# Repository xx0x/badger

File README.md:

# The Badger

The Badger is an open-source synth that packs 18 presets – synths, drums, and drones – into a small, pocketable device. Use the knobs to steer its internal generative sequencer and tweak the melodies yourself, or hit the randomizer to discover new patterns and textures at the press of a button. It also comes with MIDI (both TRS and USB), CV, and clock connections for patching into a bigger setup – or chaining multiple Badgers together. The audio is not particularly hi-fi, but that's exactly where the fun lives. Take it with a grain of salt, but: “the cheapest, *fully featured* synth ever.”

See [badger-quick-guide-en.pdf](./manuals/badger-quick-guide-en.pdf) for the quick guide.

See [badger-full-manual-en.md](./manuals/badger-full-manual-en.md) or [badger-full-manual-en.pdf](./manuals/badger-full-manual-en.pdf) for the full user manual (controls, presets, MIDI...).

## Technical Specs

- PY32F071C1BU6TR ARM Cortex M0+
- 48 MHz clock speed
- 16 kB RAM, 128 kB FLASH
- 256 B EEPROM to store settings
- MIDI in, MIDI out (TRS Jack, Type A)
- USB MIDI
- Stereo audio out using a 12-bit DAC
- Headphone amplifier with 200mW per channel at 32Ω load
- Patch points for analog clock in and out
- Banana-style holes for CV IN (0.25V to 5V), ground, True (5V ref), False (0V ref)

## Schematic

## Firmware update

Download the UF2 firmware from the *Releases*. Connect The Badger to your computer, hold *PREV* and turn the device on. The *PREV* LED should light red. Then just drag the UF2 file onto the *BADGERBOOT* drive. This applies to already built Badgers. When you build your own Badger from scratch, you need to flash the bootloader first. See [HOW_TO_DEVELOP.md](./HOW_TO_DEVELOP.md).

## Where to get it?

The Badger DIY kit is not available for purchase yet, so follow for updates.

But you can already make your own by downloading the manufacturing files from the `pcb` directory and have the PCB manufactured yourself.

## AI usage and transparency

All creative decisions – sound design, controls and layouts – were made by the author. AI tools (specifically Claude Opus 5 and 5.5) were used to help write parts of the code, fix bugs, validate the electronics design and write documentation. All AI-assisted work was reviewed and tested by the author.

## License

| What                                   | Where                                                         | License                                                   |
| -------------------------------------- | ------------------------------------------------------------- | --------------------------------------------------------- |
| Code                                   | `code/`, `utils/`                                             | MIT, see [LICENSE](./LICENSE)                             |
| Hardware design                        | `pcb/`                                                        | CERN-OHL-P-2.0, see [LICENSE-CERN-OHL-P-2.0](./LICENSE-CERN-OHL-P-2.0) |
| Documentation, manuals, images, 3D files | `manuals/`, `images/`, `3d_models/`, `*.md`                 | CC BY 4.0, see [LICENSE-CC-BY-4.0](./LICENSE-CC-BY-4.0)   |

Third-party components listed below keep their own licenses.

## Third-party components

| Component                                                                   | Where                                                                         | License                                                             |
| --------------------------------------------------------------------------- | ----------------------------------------------------------------------------- | ------------------------------------------------------------------- |
| CMSIS (Arm)                                                                 | `code/lib/CMSIS` (except `Device`)                                            | Apache-2.0                                                          |
| PY32F071 HAL driver, CMSIS device files, linker script (Puya Semiconductor) | `code/lib/PY32F071_HAL_Driver`, `code/lib/CMSIS/Device`, `code/lib/LDScripts` | BSD-3-Clause, see [LICENSE](./code/lib/PY32F071_HAL_Driver/LICENSE) |
| PY32 J-Link device support files (Puya Semiconductor)                       | `code/misc/JLinkDevices`                                                      | © Puya Semiconductor                                                |
| TinyUSB                                                                     | `code/lib/tinyusb` (submodule)                                                | MIT                                                                 |
| UF2 (Microsoft)                                                             | `code/lib/uf2` (submodule)                                                    | MIT                                                                 |
| TinyUF2 bootloader (Badger port)                                            | `code/bootloader` (prebuilt)                                                  | MIT                                                                 |
| Dosis font                                                                  | `utils/fonts/Dosis`                                                           | SIL OFL 1.1, see [OFL.txt](./utils/fonts/Dosis/OFL.txt)             |
| UnifrakturCook font (j. 'mach' wust, Peter Wiegel)                          | `utils/fonts/UnifrakturCook`                                                  | SIL OFL 1.1, see [OFL.txt](./utils/fonts/UnifrakturCook/OFL.txt)    |
| Component 3D models (from their manufacturers)                              | `pcb/badger_v2/3d_models`                                                     | Their respective owners                                             |

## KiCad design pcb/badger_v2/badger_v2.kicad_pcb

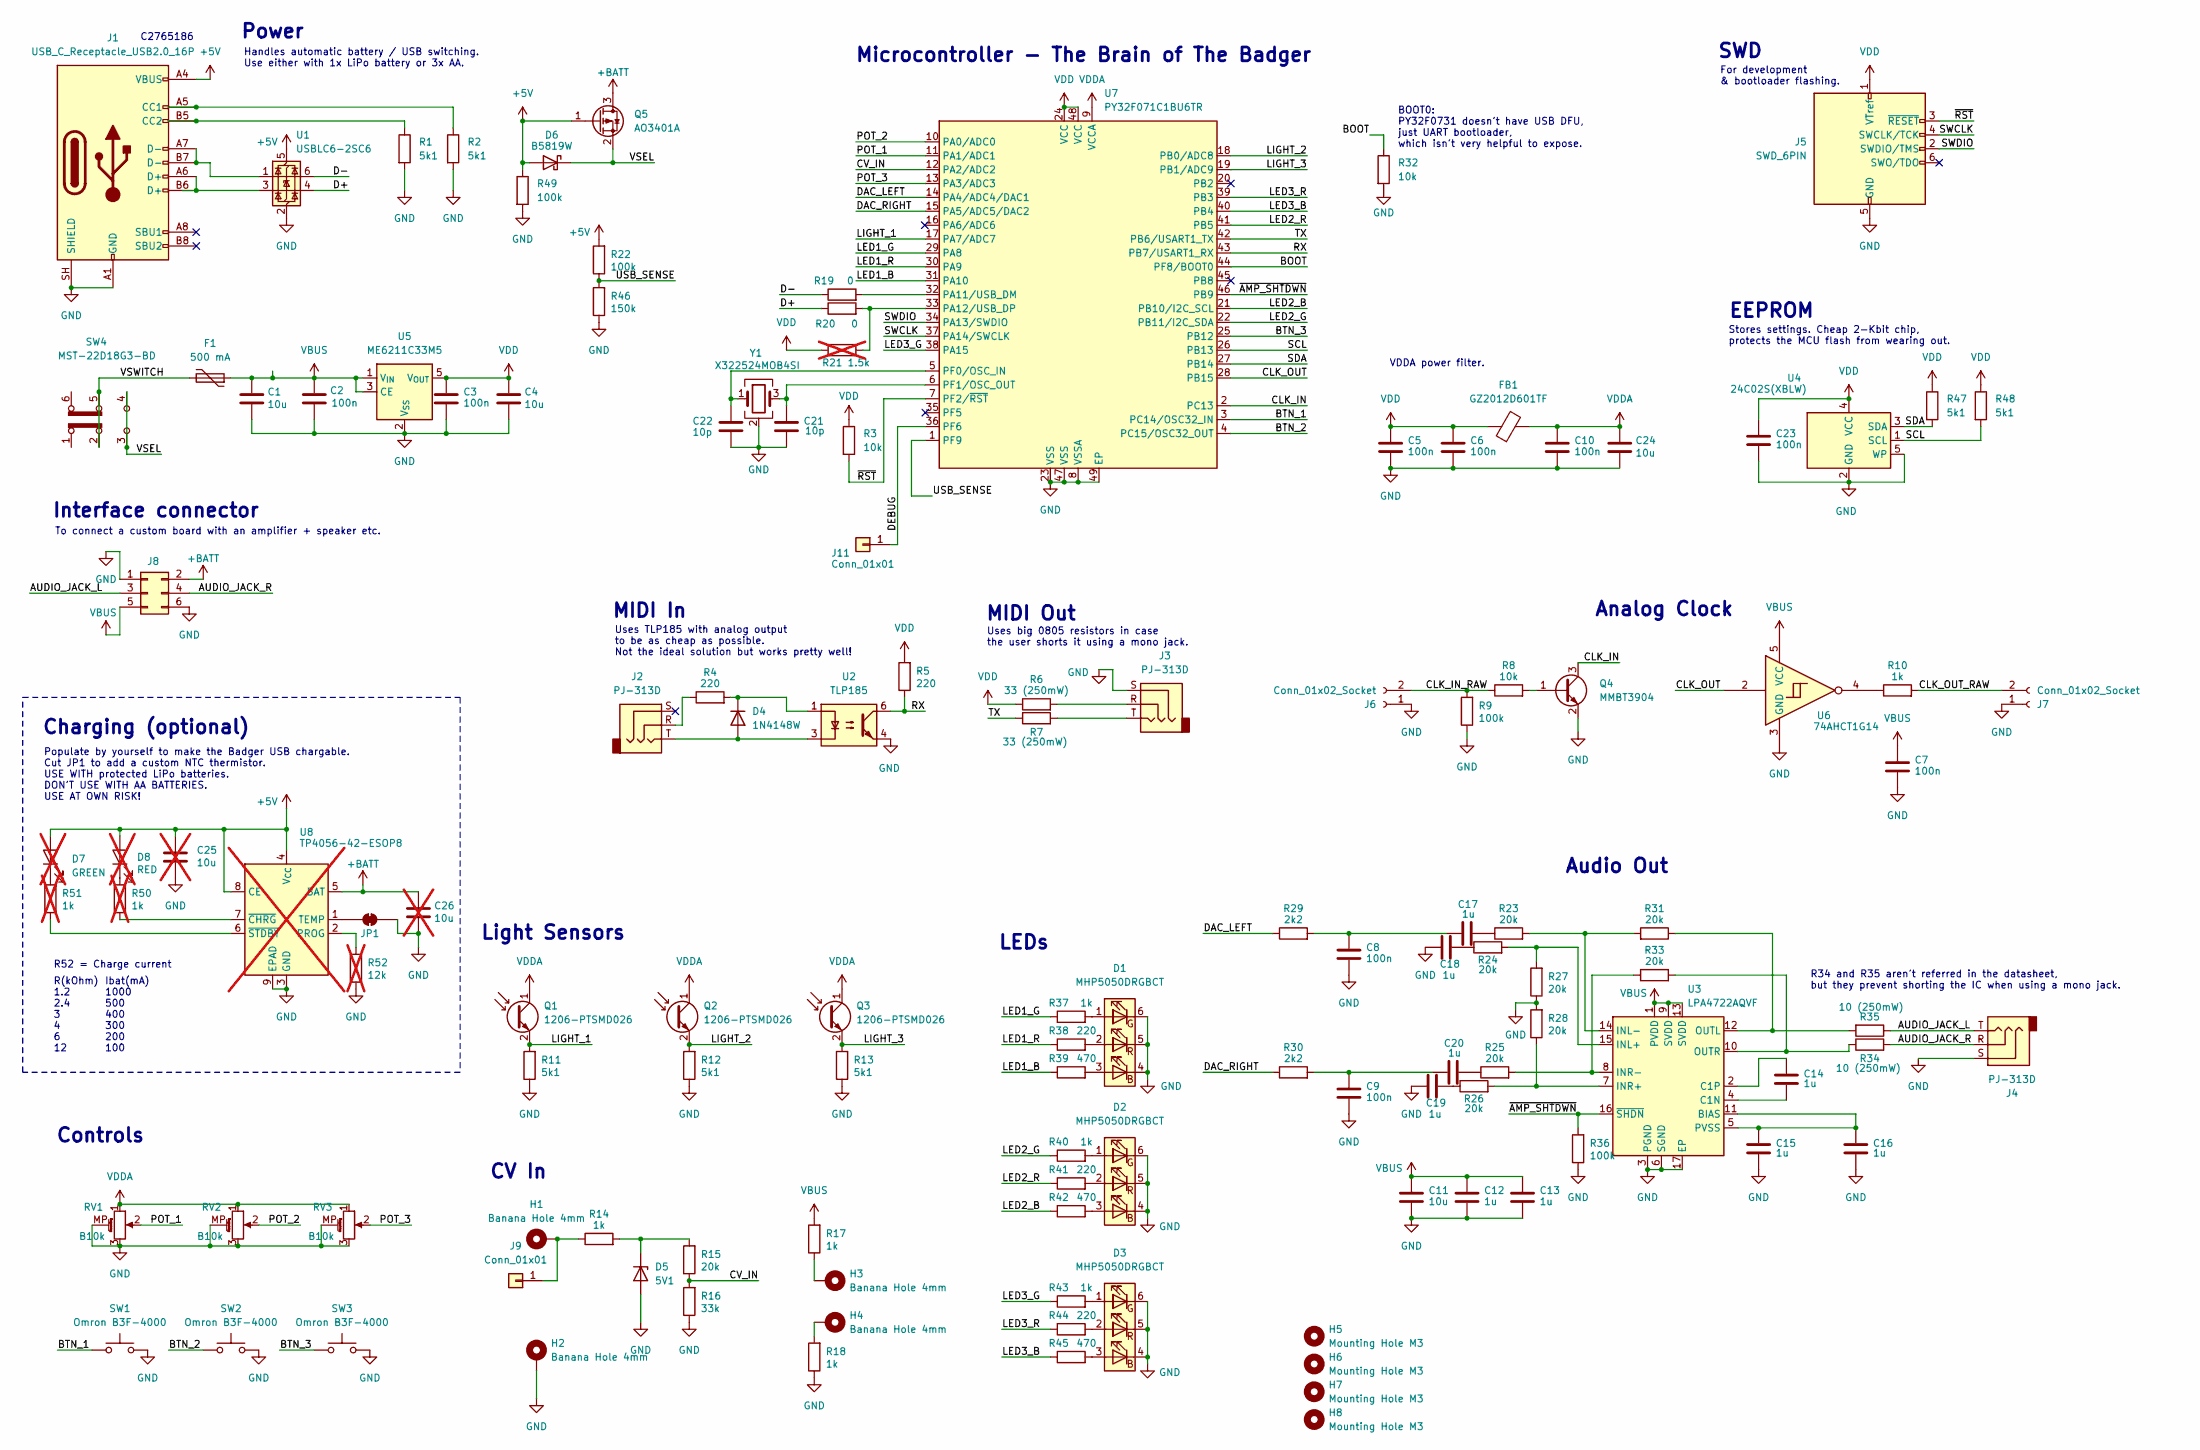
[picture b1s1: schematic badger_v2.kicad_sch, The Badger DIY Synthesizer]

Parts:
C1, C4, C11, C24: 10u; C_0603_1608Metric
C2, C3, C5, C6, C7, C8, C9, C10, C23: 100n; C_0603_1608Metric
C12, C13, C14, C15, C16, C17, C18, C19, C20: 1u; C_0603_1608Metric
C21, C22: 10p; C_0603_1608Metric
C25, C26: 10u; C_0603_1608Metric; not fitted
D1, D2, D3: MHP5050DRGBCT; LED_RGB_5050-6
D4: 1N4148W; D_SOD-123
D5: 5V1; D_SOD-123
D6: B5819W; D_SOD-123
D7: GREEN; LED_0805_2012Metric_Pad1.15x1.40mm_HandSolder; not fitted
D8: RED; LED_0805_2012Metric_Pad1.15x1.40mm_HandSolder; not fitted
F1: 500 mA; Fuse_0805_2012Metric
FB1: GZ2012D601TF; L_0805_2012Metric
H1, H2, H3, H4: Banana Hole 4mm; BananaHole_4mm
H5, H6, H7, H8: Mounting Hole M3; MountingHole_3.2mm_M3
J1: USB_C_Receptacle_USB2.0_16P; TYPE-C-31-M-12
J2, J3, J4: PJ-313D; Jack_3.5mm_PJ-313D
J5: SWD_6PIN; PinHeader_2x03_P2.54mm_Vertical
J6, J7: Conn_01x02_Socket; PinSocket_1x02_P2.54mm_Vertical
J8: Conn_02x03_Odd_Even; IDC-Header_2x03_P2.54mm_Vertical
J9, J11: Conn_01x01; PinHeader_1x01_P2.54mm_Vertical_Round_NoSilk
JP1: SolderJumper_2_Bridged; SolderJumper-2_P1.3mm_Bridged_RoundedPad1.0x1.5mm
Q1, Q2, Q3: 1206-PTSMD026; Phototransistor
Q4: MMBT3904; SOT-23
Q5: AO3401A; SOT-23
R1, R2, R11, R12, R13, R47, R48: 5k1; R_0603_1608Metric
R3, R8, R32: 10k; R_0603_1608Metric
R4, R5, R38, R41, R44: 220; R_0603_1608Metric
R6, R7: 33 (250mW); R_0805_2012Metric
R9, R22, R36, R49: 100k; R_0603_1608Metric
R10, R14, R17, R18, R37, R40, R43: 1k; R_0603_1608Metric
R15, R23, R24, R25, R26, R27, R28, R31, R33: 20k; R_0603_1608Metric
R16: 33k; R_0603_1608Metric
R19, R20: 0; R_0603_1608Metric
R21: 1.5k; R_0603_1608Metric; not fitted
R29, R30: 2k2; R_0603_1608Metric
R34, R35: 10 (250mW); R_0805_2012Metric
R39, R42, R45: 470; R_0603_1608Metric
R46: 150k; R_0603_1608Metric
R50, R51: 1k; R_0603_1608Metric; not fitted
R52: 12k; R_0603_1608Metric; not fitted
RV1, RV2, RV3: B10k; PotAlpha_Plastic
SW1, SW2, SW3: Omron B3F-4000; SW_SPST_Omron_B3F-40xx_CENTER
SW4: MST-22D18G3-BD
U1: USBLC6-2SC6; SOT-23-6
U2: TLP185; SOIC-4_4.55x3.7mm_P2.54mm
U3: LPA4722AQVF; WQFN-16-1EP_3x3mm_P0.5mm_EP1.6x1.6mm_ThermalVias
U4: 24C02S(XBLW); SOT-23-5
U5: ME6211C33M5; SOT-23-5
U6: 74AHCT1G14; SOT-23-5
U7: PY32F071C1BU6TR; QFN-48-1EP_6x6mm_P0.4mm_EP4.3x4.3mm
U8: TP4056-42-ESOP8; SOIC-8-1EP_3.9x4.9mm_P1.27mm_EP2.41x3.3mm_ThermalVias; not fitted
Y1: X322524MOB4SI; Crystal_SMD_3225-4Pin_3.2x2.5mm

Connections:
+5V: C25.1, D6.2 (A), D7.2 (A), D8.2 (A), J1.A4 (VBUS), J1.A9 (VBUS), J1.B4 (VBUS), J1.B9 (VBUS), Q5.1 (G), R22.2, R49.1, U1.5 (VBUS), U8.4 (V_{CC}), U8.8 (CE)
+BATT: C26.1, J8.2, Q5.3 (D), U8.5 (BAT)
/AUDIO_JACK_L: J4.T, J8.3, R35.1
/AUDIO_JACK_R: J4.R, J8.4, R34.2
/BOOT: R32.1, U7.44 (PF8/BOOT0)
/BTN_1: SW1.1, U7.3 (PC14/OSC32_IN)
/BTN_2: SW2.1, U7.4 (PC15/OSC32_OUT)
/BTN_3: SW3.1, U7.25 (PB12)
/CLK_IN: Q4.3 (C), U7.2 (PC13)
/CLK_IN_RAW: J6.2, R8.1, R9.2
/CLK_OUT: U6.2, U7.28 (PB15)
/CLK_OUT_RAW: J7.2, R10.2
/CV_IN: R15.1, R16.2, U7.12 (PA2/ADC2)
/D+: R20.1, U1.4 (I/O2)
/D-: R19.1, U1.6 (I/O1)
/DAC_LEFT: R29.1, U7.14 (PA4/ADC4/DAC1)
/DAC_RIGHT: R30.1, U7.15 (PA5/ADC5/DAC2)
/DEBUG: J11.1 (Pin_1_1), U7.36 (PF6)
/LED1_B: R39.1, U7.31 (PA10)
/LED1_G: R37.1, U7.29 (PA8)
/LED1_R: R38.1, U7.30 (PA9)
/LED2_B: R42.1, U7.21 (PB10/I2C_SCL)
/LED2_G: R40.1, U7.22 (PB11/I2C_SDA)
/LED2_R: R41.1, U7.41 (PB5)
/LED3_B: R45.1, U7.40 (PB4)
/LED3_G: R43.1, U7.38 (PA15)
/LED3_R: R44.1, U7.39 (PB3)
/LIGHT_1: Q1.2 (E), R11.2, U7.17 (PA7/ADC7)
/LIGHT_2: Q2.2 (E), R12.2, U7.18 (PB0/ADC8)
/LIGHT_3: Q3.2 (E), R13.2, U7.19 (PB1/ADC9)
/POT_1: RV1.2, U7.11 (PA1/ADC1)
/POT_2: RV2.2, U7.10 (PA0/ADC0)
/POT_3: RV3.2, U7.13 (PA3/ADC3)
/RX: R5.1, U2.6, U7.43 (PB7/USART1_RX)
/SCL: R48.2, U4.1 (SCL), U7.26 (PB13)
/SDA: R47.2, U4.3 (SDA), U7.27 (PB14)
/SWCLK: J5.4 (SWCLK/TCK), U7.37 (PA14/SWCLK)
/SWDIO: J5.2 (SWDIO/TMS), U7.34 (PA13/SWDIO)
/TX: R7.1, U7.42 (PB6/USART1_TX)
/USB_SENSE: R22.1, R46.2, U7.1 (PF9)
/VSEL: D6.1 (K), Q5.2 (S), SW4.3 (C), SW4.4 (A)
/VSWITCH: F1.2, SW4.2 (B), SW4.5 (B)
/~AMP_SHTDWN: R36.2, U3.16 (~SHDN), U7.46 (PB9)
/~RST: J5.3 (~RESET), R3.2, U7.7 (PF2/~RST)
GND: C1.2, C2.2, C3.2, C4.2, C5.2, C6.2, C7.2, C8.2, C9.2, C10.2, C11.2, C12.2, C13.2, C15.2, C16.2, C18.1, C19.1, C21.1, C22.1, C23.2, C24.2, C25.2, C26.2, D1.4 (BK), D1.5 (RK), D1.6 (GK), D2.4 (BK), D2.5 (RK), D2.6 (GK), D3.4 (BK), D3.5 (RK), D3.6 (GK), D5.2 (A), H2.1 (1_1), J1.A1 (GND), J1.A12 (GND), J1.B1 (GND), J1.B12 (GND), J1.SH (SHIELD), J3.S, J4.S, J5.5 (GND), J6.1, J7.1, J8.1, J8.6, JP1.2 (B), Q4.2 (E), R1.2, R2.2, R9.1, R11.1, R12.1, R13.1, R16.1, R18.1, R27.1, R28.2, R32.2, R36.1, R46.1, R49.2, R52.1, RV1.3, RV1.MP (MountPin), RV2.3, RV2.MP (MountPin), RV3.3, RV3.MP (MountPin), SW1.2, SW2.2, SW3.2, U1.2 (GND), U2.4, U3.3 (PGND), U3.6 (SGND), U3.17 (EP), U4.2 (GND), U4.5 (WP), U5.2 (V_{SS}), U6.3 (GND), U7.8 (VSSA), U7.23 (VSS), U7.47 (VSS), U7.49 (EP), U8.3 (GND), U8.9 (EPAD), Y1.2 (G), Y1.4 (G)
unnamed: C8.1, C17.1, R29.2
unnamed: C17.2, R23.1
unnamed: C18.2, R24.1
unnamed: C19.2, R26.1
unnamed: C9.1, C20.1, R30.2
unnamed: C20.2, R25.1
unnamed: D1.3 (BA), R39.2
unnamed: D1.1 (GA), R37.2
unnamed: D1.2 (RA), R38.2
unnamed: D2.3 (BA), R42.2
unnamed: D2.1 (GA), R40.2
unnamed: D2.2 (RA), R41.2
unnamed: D3.3 (BA), R45.2
unnamed: D3.1 (GA), R43.2
unnamed: D3.2 (RA), R44.2
unnamed: D4.2 (A), J2.T, U2.3
unnamed: D4.1 (K), R4.2, U2.1
unnamed: D5.1 (K), R14.2, R15.2
unnamed: D7.1 (K), R51.2
unnamed: D8.1 (K), R50.2
unnamed: H3.1 (1_1), R17.1
unnamed: H4.1 (1_1), R18.2
unnamed: J1.A5 (CC1), R2.1
unnamed: J1.B5 (CC2), R1.1
unnamed: J1.A6 (D+), J1.B6 (D+), U1.3 (I/O2)
unnamed: J1.A7 (D-), J1.B7 (D-), U1.1 (I/O1)
unnamed: J2.R, R4.1
unnamed: J3.R, R6.2
unnamed: J3.T, R7.2
unnamed: H1.1 (1_1), J9.1 (Pin_1_1), R14.1
unnamed: JP1.1 (A), U8.1 (TEMP)
unnamed: Q4.1 (B), R8.2
unnamed: R10.1, U6.4
unnamed: C15.1, C16.1, U3.5 (PVSS), U3.11 (BIAS)
unnamed: C14.2, U3.4 (C1N)
unnamed: C14.1, U3.2 (C1P)
unnamed: R24.2, R27.2, U3.15 (INL+)
unnamed: R23.2, R31.2, U3.14 (INL-)
unnamed: R26.2, R28.1, U3.7 (INR+)
unnamed: R25.2, R33.1, U3.8 (INR-)
unnamed: R31.1, R35.2, U3.12 (OUTL)
unnamed: R33.2, R34.1, U3.10 (OUTR)
unnamed: R19.2, U7.32 (PA11/USB_DM)
unnamed: R20.2, R21.1, U7.33 (PA12/USB_DP)
unnamed: C22.2, U7.5 (PF0/OSC_IN), Y1.1
unnamed: C21.2, U7.6 (PF1/OSC_OUT), Y1.3
unnamed: R52.2, U8.2 (PROG)
unnamed: R50.1, U8.7 (~CHRG)
unnamed: R51.1, U8.6 (~STDBY)
VBUS: C1.1, C2.1, C7.1, C11.1, C12.1, C13.1, F1.1, J8.5, R17.2, U3.1 (PVDD), U3.9 (SVDD), U3.13 (SVDD), U5.1 (V_{IN}), U5.3 (CE), U6.5 (VCC)
VDD: C3.1, C4.1, C5.1, C6.1, C23.1, FB1.1, J5.1 (VTref), R3.1, R5.2, R6.1, R21.2, R47.1, R48.1, U4.4 (VCC), U5.5 (V_{OUT}), U7.24 (VCC), U7.48 (VCC)
VDDA: C10.1, C24.1, FB1.2, Q1.1 (C), Q2.1 (C), Q3.1 (C), RV1.1, RV2.1, RV3.1, U7.9 (VCCA)

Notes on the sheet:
Audio Out
Uses TLP185 with analog output to be as cheap as possible. Not the ideal solution but works pretty well!
Uses big 0805 resistors in case the user shorts it using a mono jack.
C2765186
EEPROM
Controls
Stores settings. Cheap 2-Kbit chip, protects the MCU flash from wearing out.
R34 and R35 aren't referred in the datasheet, but they prevent shorting the IC when using a mono jack.
Handles automatic battery / USB switching. Use either with 1x LiPo battery or 3x AA.
VDDA power filter.
Microcontroller - The Brain of The Badger
Analog Clock
To connect a custom board with an amplifier + speaker etc.
SWD
BOOT0: PY32F0731 doesn't have USB DFU, just UART bootloader, which isn't very helpful to expose.
MIDI Out
Charging (optional)
R52 = Charge current
CV In
Interface connector
Populate by yourself to make the Badger USB chargable. Cut JP1 to add a custom NTC thermistor. USE WITH protected LiPo batteries. DON'T USE WITH AA BATTERIES. USE AT OWN RISK!
For development & bootloader flashing.
Ibat(mA) 1000 500 400 300 200 100
Light Sensors
MIDI In
R(kOhm) 1.2 2.4 3 4 6 12
LEDs
Power

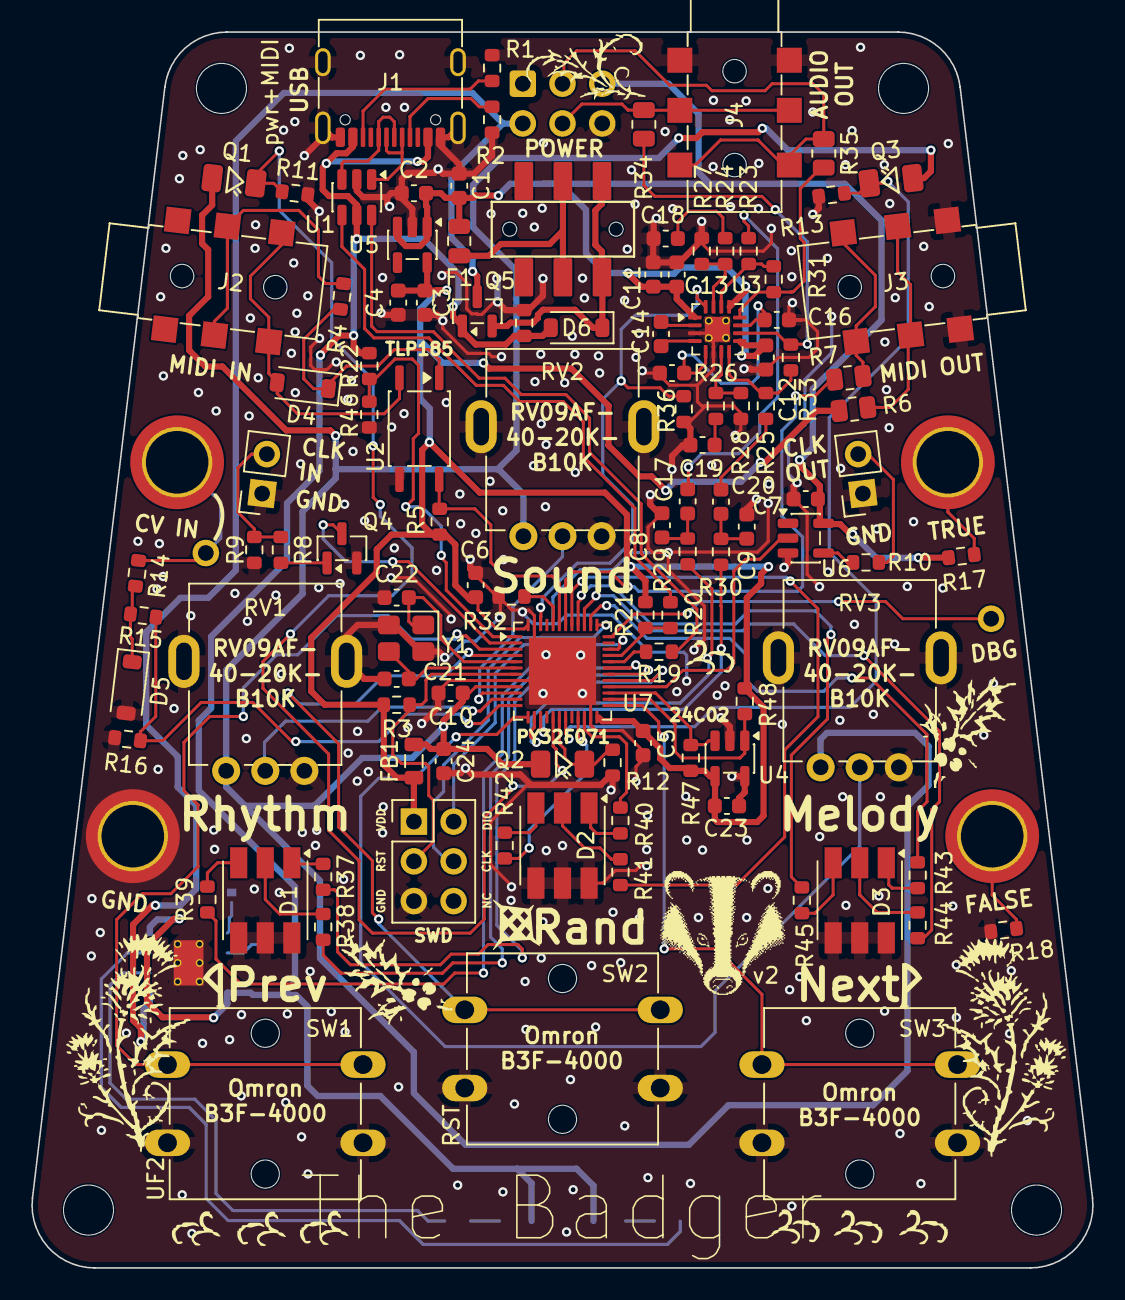
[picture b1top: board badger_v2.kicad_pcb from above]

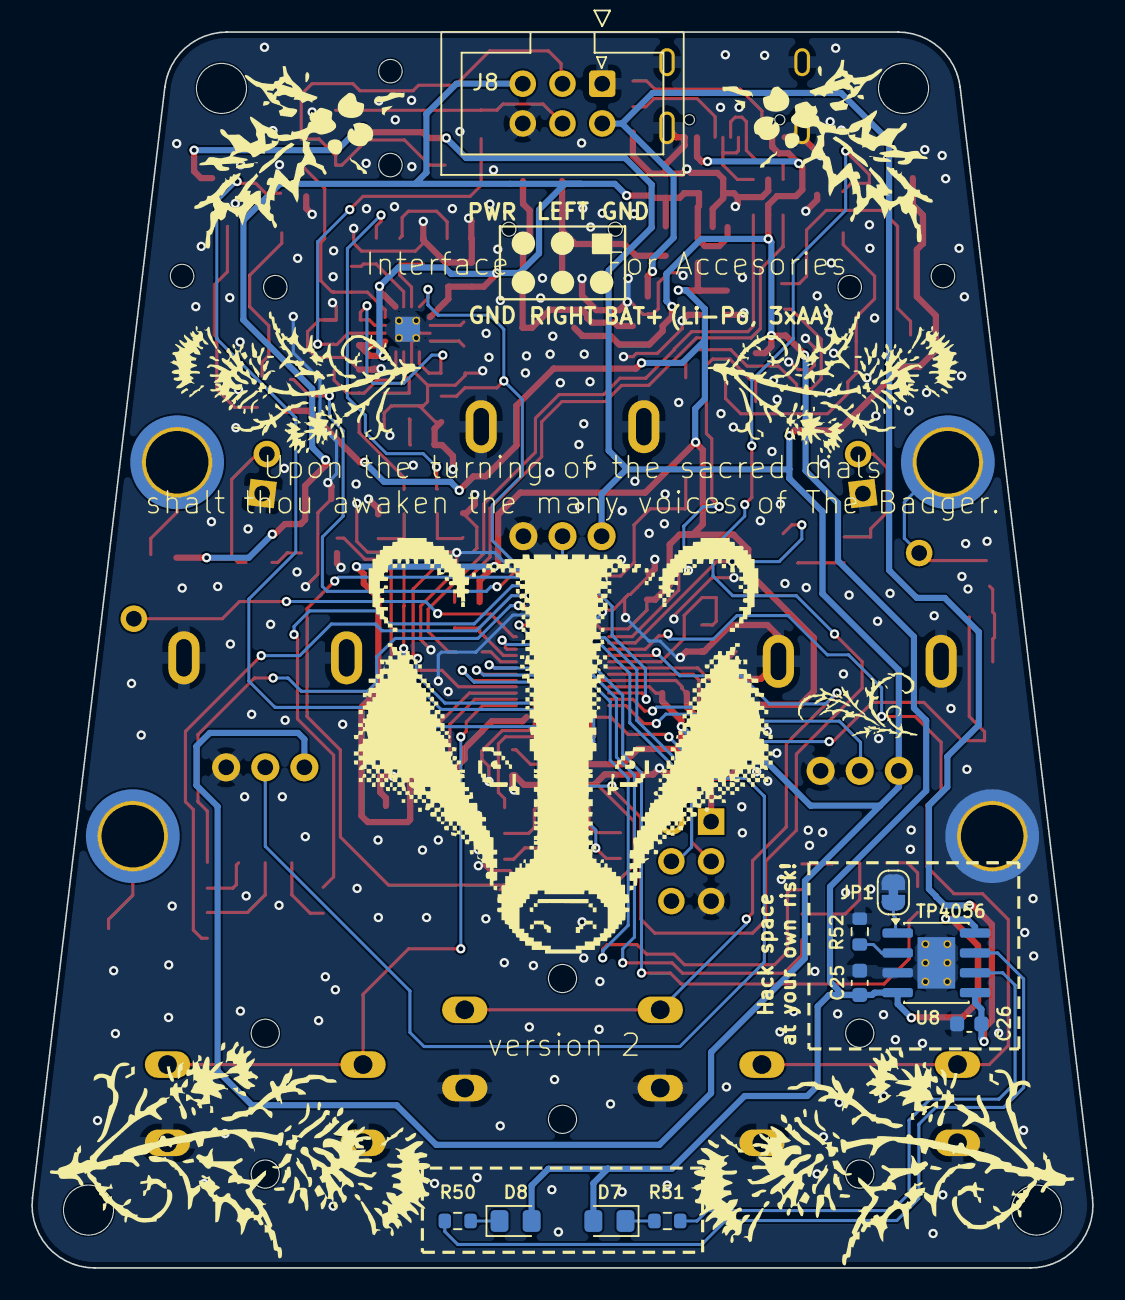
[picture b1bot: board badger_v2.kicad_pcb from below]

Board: 2 copper layers, 67.8 x 79.0 mm, 128 parts (10 on the bottom side), 97 nets.

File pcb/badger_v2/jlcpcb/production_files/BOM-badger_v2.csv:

Comment,Designator,Footprint,LCSC,Quantity
0,"R19,R20",R_0603_1608Metric,C21189,2
10 (250mW),"R34,R35",R_0805_2012Metric,C317221,2
100k,"R22,R36,R49,R9",R_0603_1608Metric,C25803,4
100n,"C10,C2,C23,C3,C5,C6,C7,C8,C9",C_0603_1608Metric,C14663,9
10k,"R3,R32,R8",R_0603_1608Metric,C25804,3
10p,"C21,C22",C_0603_1608Metric,C1634,2
10u,"C1,C11,C24,C4",C_0603_1608Metric,C19702,4
1206-PTSMD026,"Q1,Q2,Q3",Phototransistor,C242255,3
150k,R46,R_0603_1608Metric,C22807,1
1N4148W,D4,D_SOD-123,C81598,1
1k,"R10,R14,R17,R18,R37,R40,R43",R_0603_1608Metric,C21190,7
1u,"C12,C13,C14,C15,C16,C17,C18,C19,C20",C_0603_1608Metric,C15849,9
20k,"R15,R23,R24,R25,R26,R27,R28,R31,R33",R_0603_1608Metric,C4184,9
220,"R38,R4,R41,R44,R5",R_0603_1608Metric,C22962,5
24C02S(XBLW),U4,SOT-23-5,C18723540,1
2k2,"R29,R30",R_0603_1608Metric,C4190,2
33 (250mW),"R6,R7",R_0805_2012Metric,C17634,2
33k,R16,R_0603_1608Metric,C4216,1
470,"R39,R42,R45",R_0603_1608Metric,C23179,3
500 mA,F1,Fuse_0805_2012Metric,C2977522,1
5V1,D5,D_SOD-123,C19077401,1
5k1,"R1,R11,R12,R13,R2,R47,R48",R_0603_1608Metric,C23186,7
74AHCT1G14,U6,SOT-23-5,C55144666,1
AO3401A,Q5,SOT-23,C15127,1
B5819W,D6,D_SOD-123,C8598,1
GZ2012D601TF,FB1,L_0805_2012Metric,C1017,1
LPA4722AQVF,U3,WQFN-16-1EP_3x3mm_P0.5mm_EP1.6x1.6mm_ThermalVias,C517163,1
ME6211C33M5,U5,SOT-23-5,C82942,1
MHP5050DRGBCT,"D1,D2,D3",LED_RGB_5050-6,C7470880,3
MMBT3904,Q4,SOT-23,C20526,1
MST-22D18G3-BD,SW4,MST-22D18G3-BD,C7507441,1
PJ-313D,"J2,J3,J4",Jack_3.5mm_PJ-313D,C668608,3
PY32F071C1BU6TR,U7,QFN-48-1EP_6x6mm_P0.4mm_EP4.3x4.3mm,C7434410,1
TLP185,U2,SOIC-4_4.55x3.7mm_P2.54mm,C388375,1
USBLC6-2SC6,U1,SOT-23-6,C2687116,1
USB_C_Receptacle_USB2.0_16P,J1,TYPE-C-31-M-12,C2765186,1
X322524MOB4SI,Y1,Crystal_SMD_3225-4Pin_3.2x2.5mm,C70590,1

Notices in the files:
pcb/badger_v2/badger_v2.kicad_pcb:
author: Václav Mach, license: CERN-OHL-P-2.0
